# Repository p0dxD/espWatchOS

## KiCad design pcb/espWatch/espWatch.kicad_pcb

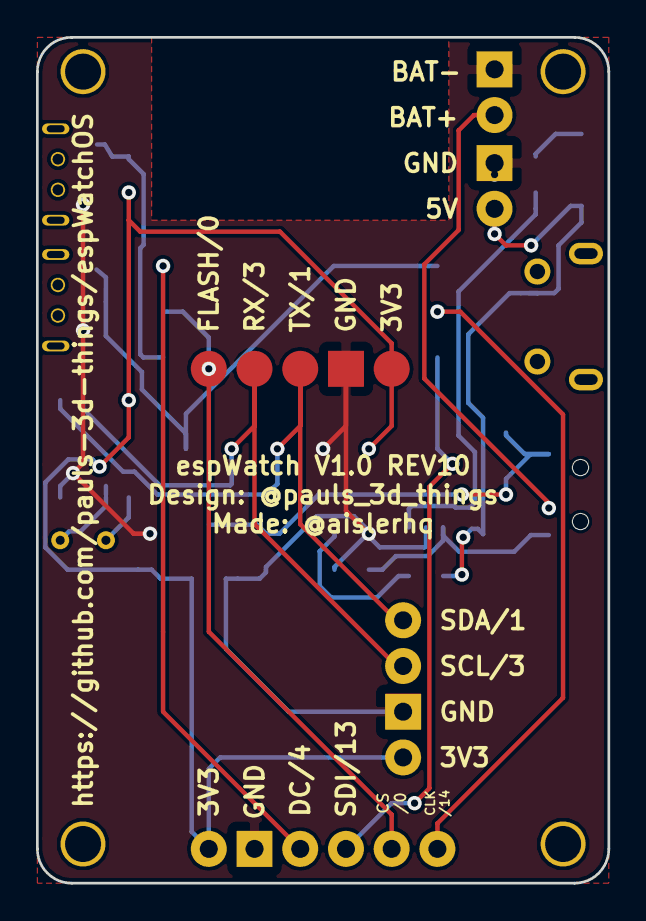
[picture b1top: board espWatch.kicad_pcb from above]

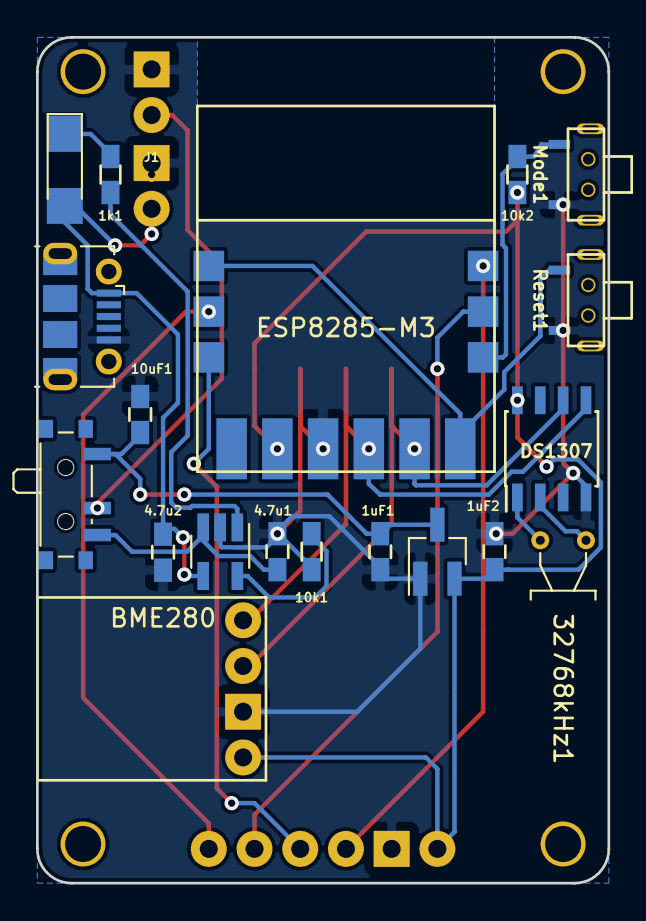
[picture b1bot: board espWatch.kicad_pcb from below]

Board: 2 copper layers, 31.8 x 47.0 mm, 23 parts (20 on the bottom side), 19 nets.

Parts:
1k1: R_LED; R_0603_HandSoldering_narrow
1uF1: Cin; C_0603_HandSoldering_narrow
1uF2: Cout; C_0603_HandSoldering_narrow
4.7u1, 4.7u2: C_Small; C_0603_HandSoldering_narrow
10k1: R_PROG; R_0603_HandSoldering_narrow
10k2: R_Mode; R_0603_HandSoldering_narrow
10uF1: CAP_VIN; C_0603_HandSoldering_narrow
32768kHz1: CRYSTAL; Crystal_AT310_D3.0mm_L10.0mm_Horizontal_1EP_style1
BME280: BME280
CHG/ON1: SWITCH; SW_SPDT_PCM12
D1: LED_Status; LED_1206_HandSoldering_wide
ESP8285-M3: esp8285-m3
J1: BAT; Pin_Header_Straight_1x02_Pitch2.54mm
J2: USB_A; USB_Micro-B_Molex-105017-0001
J3: DISPLAY; Pin_Header_Straight_1x06_Pitch2.54mm
MCP73831: mcp73831; SOT-23-5_HandSoldering
Mode1: SW_MODE; button_side_smd
Programmer1: Programmer; Pin_Header_Straight_1x05_Pitch2.54mm
Reset1: SW_RST; button_side_smd
Solar1: Solar; Pin_Header_Straight_1x02_Pitch2.54mm
U4: DS1307+; SOIC-8_3.9x4.9mm_P1.27mm
U5: MCP1700-3302E_SOT23; SOT-23_Handsoldering

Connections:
+3V3: 1uF2.1, 10k2.1, BME280.1, ESP8285-M3.5, J3.6, Programmer1.5, U4.8, U5.2
+3V8: 1uF1.1, 10uF1.1, CHG/ON1.1, U5.3
+5V: 4.7u2.1, D1.2, J2.1, MCP73831.4, Solar1.1
/BAT+: CHG/ON1.2, J1.1
/BTN_MODE: 10k2.2, ESP8285-M3.10, Mode1.1
/CLK: ESP8285-M3.2, J3.1
/CS: ESP8285-M3.11, J3.2, Programmer1.1
/DC: ESP8285-M3.12, J3.4
/RST: ESP8285-M3.1, ESP8285-M3.9, Reset1.1
/SCL: BME280.3, ESP8285-M3.8, Programmer1.2, U4.6
/SDA: BME280.4, ESP8285-M3.7, Programmer1.3, U4.5
/SDI: ESP8285-M3.3, J3.3
/VBAT: 4.7u1.1, CHG/ON1.3, MCP73831.3
GND: 1uF1.2, 1uF2.2, 4.7u1.2, 4.7u2.2, 10k1.1, 10uF1.2, BME280.2, ESP8285-M3.6, J1.2, J2.4, J3.5, MCP73831.2, Mode1.2, Programmer1.4, Reset1.2, Solar1.2, U4.4, U5.1
unnamed: 1k1.1, MCP73831.1
unnamed: 1k1.2, D1.1
unnamed: 10k1.2, MCP73831.5
unnamed: 32768kHz1.1, U4.1
unnamed: 32768kHz1.2, U4.2

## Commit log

2018-08-09 Use rtc module
    Save more power during sleep
2018-08-09 Test power saving
2018-08-09 BME sleep
2018-08-09 Fix ds1307 handling
2018-08-09 Improved e-ink performance, partial refresh after first boot
2018-08-10 Button test on gpio2
2018-08-10 Refactored into platformIO project, add screens
2018-08-10 Add watchfaces
2018-08-10 Add roman watchface
2018-08-10 Update blend
2018-08-10 Add icons and logo
2018-08-10 Add video link
2018-08-26 Rotate screen
2018-08-28 Add 3d model, refactor structure, cleanup watchfaces
2018-08-28 Move image headers to images/
2018-09-02 Add SensorHistory class
2018-09-02 Add charts
2018-09-02 Update docs
2018-09-02 Add Licenses
2018-09-02 Update README, test new refresh settings
2018-09-04 Add KiCad files, update Readme.md
2018-09-04 Fix typo
